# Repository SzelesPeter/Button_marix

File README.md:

# Button_marix
A simple pcb with 16 buttons in a 4x4 matric.
Created in Kicad.

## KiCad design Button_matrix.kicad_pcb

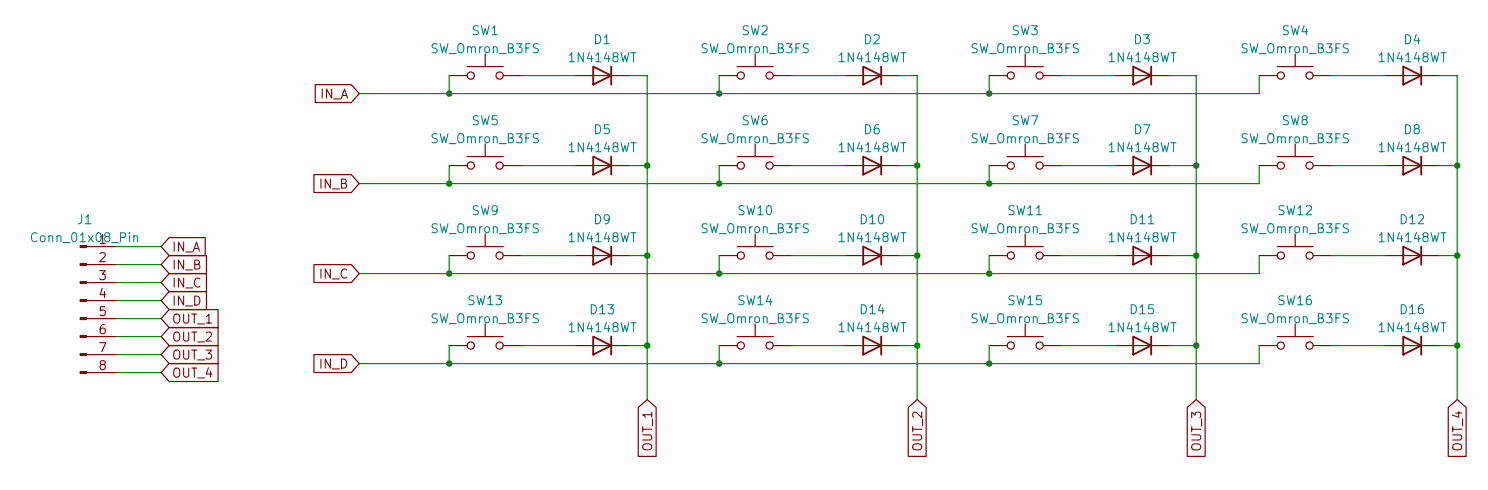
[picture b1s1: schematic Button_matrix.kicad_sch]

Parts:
D1, D2, D3, D4, D5, D6, D7, D8, D9, D10, D11, D12, D13, D14, D15, D16: 1N4148WT; D_SOD-523
J1: Conn_01x08_Pin; PinHeader_1x08_P2.54mm_Vertical
SW1, SW2, SW3, SW4, SW5, SW6, SW7, SW8, SW9, SW10, SW11, SW12, SW13, SW14, SW15, SW16: SW_Omron_B3FS; SW_SPST_Omron_B3FS-100xP

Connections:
IN_A: J1.1, SW1.1, SW2.1, SW3.1, SW4.1
IN_B: J1.2, SW5.1, SW6.1, SW7.1, SW8.1
IN_C: J1.3, SW9.1, SW10.1, SW11.1, SW12.1
IN_D: J1.4, SW13.1, SW14.1, SW15.1, SW16.1
unnamed: D1.2 (A), SW1.2
unnamed: D2.2 (A), SW2.2
unnamed: D3.2 (A), SW3.2
unnamed: D4.2 (A), SW4.2
unnamed: D5.2 (A), SW5.2
unnamed: D6.2 (A), SW6.2
unnamed: D7.2 (A), SW7.2
unnamed: D8.2 (A), SW8.2
unnamed: D9.2 (A), SW9.2
unnamed: D10.2 (A), SW10.2
unnamed: D11.2 (A), SW11.2
unnamed: D12.2 (A), SW12.2
unnamed: D13.2 (A), SW13.2
unnamed: D14.2 (A), SW14.2
unnamed: D15.2 (A), SW15.2
unnamed: D16.2 (A), SW16.2
OUT_1: D1.1 (K), D5.1 (K), D9.1 (K), D13.1 (K), J1.5
OUT_2: D2.1 (K), D6.1 (K), D10.1 (K), D14.1 (K), J1.6
OUT_3: D3.1 (K), D7.1 (K), D11.1 (K), D15.1 (K), J1.7
OUT_4: D4.1 (K), D8.1 (K), D12.1 (K), D16.1 (K), J1.8

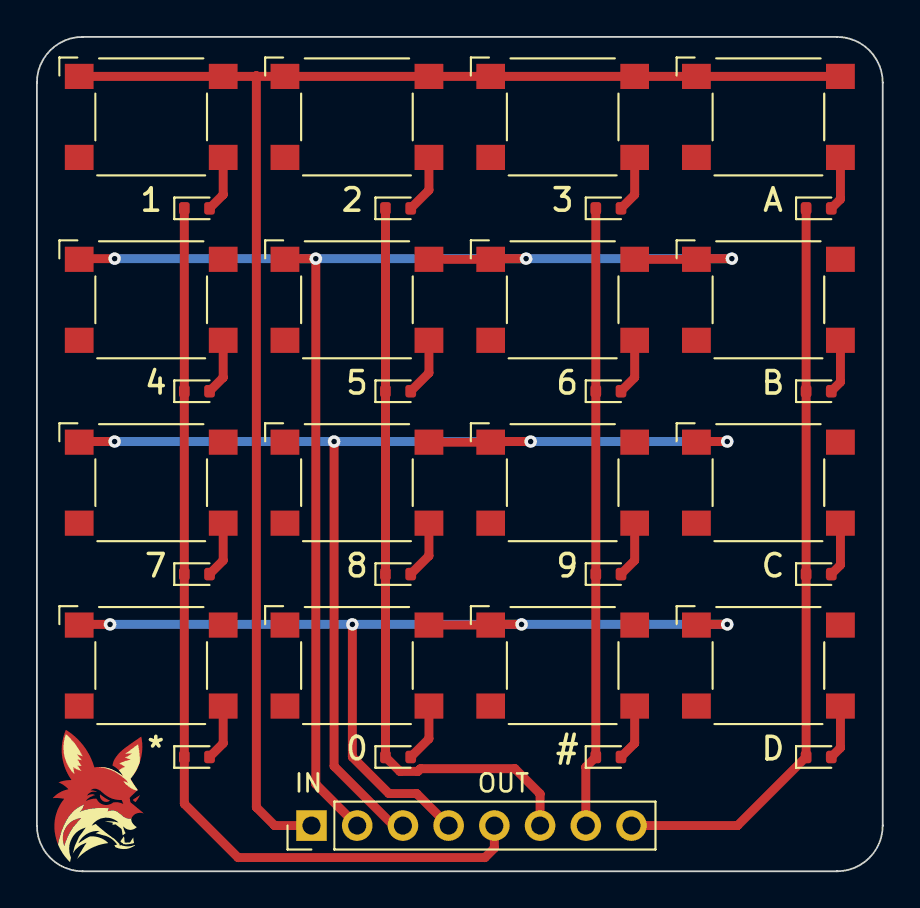
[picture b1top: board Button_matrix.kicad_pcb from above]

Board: 2 copper layers, 47.0 x 46.4 mm, 33 parts (0 on the bottom side), 24 nets.
